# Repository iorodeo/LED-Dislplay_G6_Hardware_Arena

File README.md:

## LED-Display\_ G6\_Hardware\_Arena 

This repository is part of <https://reiserlab.github.io/Modular-LED-Display/>.
It contains the KiCad design and production files for the G6 arena hardware.

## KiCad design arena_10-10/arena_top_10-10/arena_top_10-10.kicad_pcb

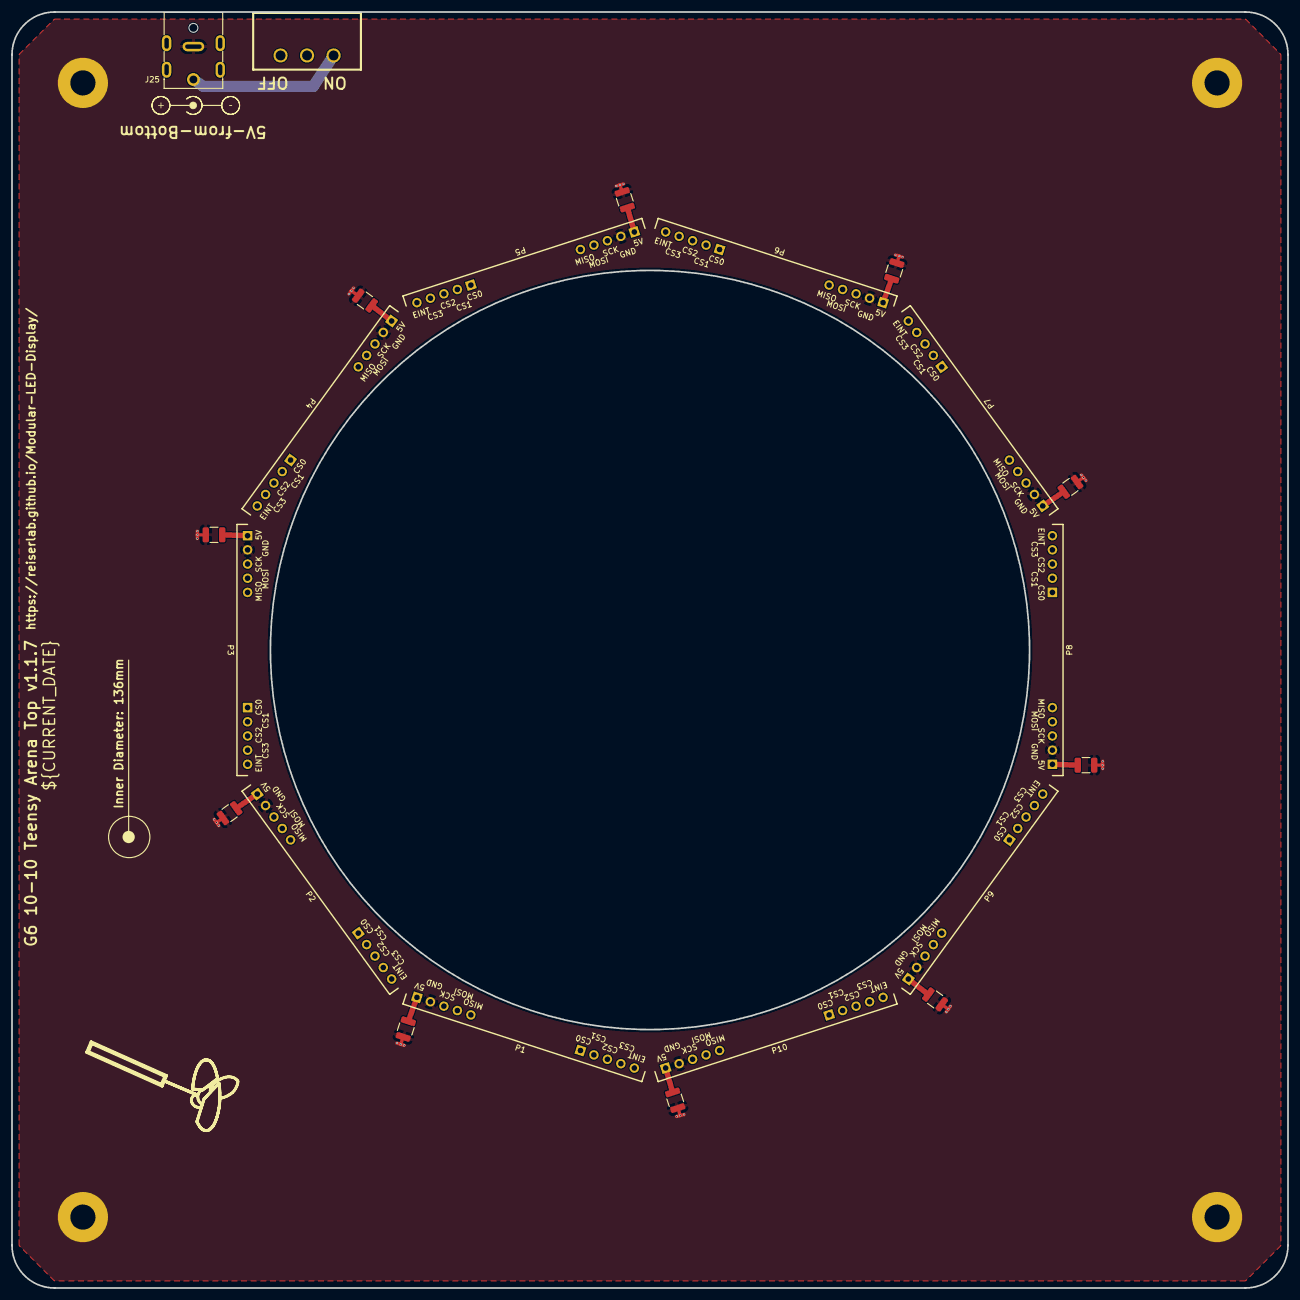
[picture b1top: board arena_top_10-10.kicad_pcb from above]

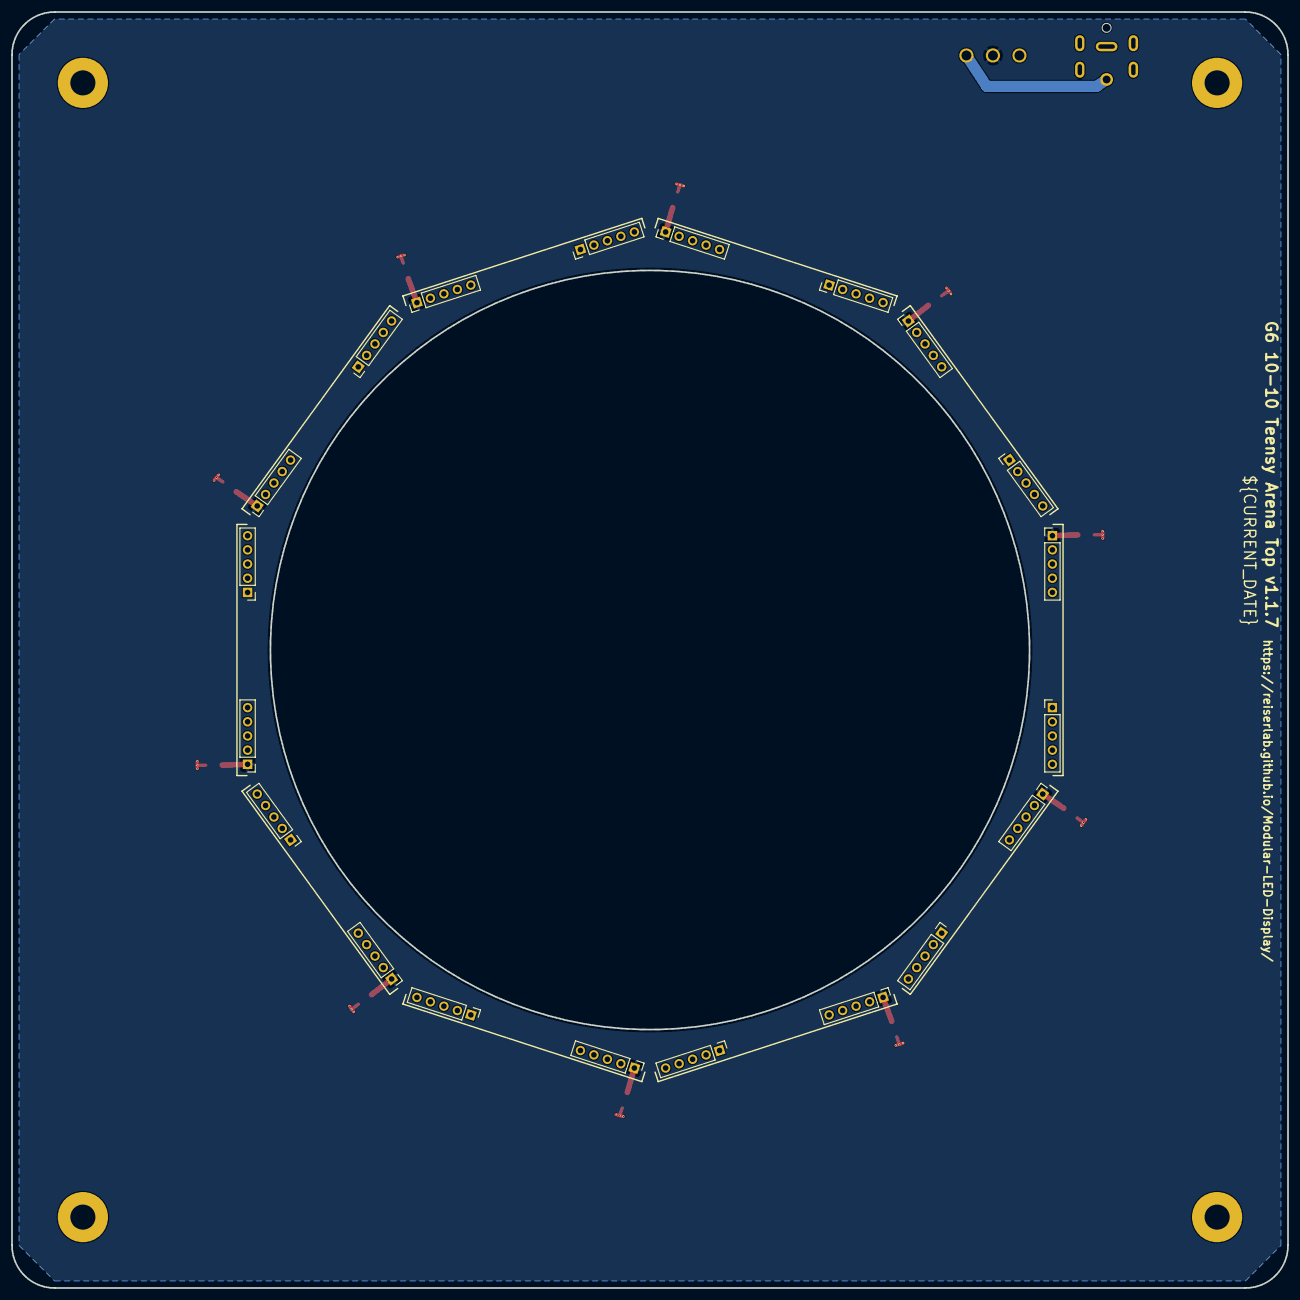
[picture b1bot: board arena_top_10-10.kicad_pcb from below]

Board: 2 copper layers, 228.6 x 228.6 mm, 46 parts (20 on the bottom side), 3 nets.

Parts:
C42, C47, C52, C57, C62, C67, C72, C77, C82, C87: 100uF; C_1210_3225Metric
H1, H2, H3, H4: MountingHole_Pad; MountingHole_4.5mm_Pad
J5, J6, J7, J8, J9, J10, J11, J12, J13, J14, J15, J16, J17, J18, J19, J20, J21, J22, J23, J24: Conn_01x05; PinHeader_1x05_P2.54mm_Vertical
J25: Barrel_Jack; DC-053D-20A
P1, P2, P3, P4, P5, P6, P7, P8, P9, P10: NA; Panel_Silk
SW1: SW_SPDT; slide_switch

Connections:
+5V: C42.2, C47.2, C52.2, C57.2, C62.2, C67.2, C72.2, C77.2, C82.2, C87.2, J5.1, J7.1, J9.1, J11.1, J13.1, J15.1, J17.1, J19.1, J21.1, J23.1, SW1.2 (B)
/Power/SW_5V: J25.1, SW1.1 (A)
GND: C42.1, C47.1, C52.1, C57.1, C62.1, C67.1, C72.1, C77.1, C82.1, C87.1, H1.1, H2.1, H3.1, H4.1, J5.2, J7.2, J9.2, J11.2, J13.2, J15.2, J17.2, J19.2, J21.2, J23.2, J25.2

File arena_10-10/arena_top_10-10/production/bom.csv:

Designator,Footprint,Quantity,Value,LCSC Part #
"C42, C47, C52, C57, C62, C67, C72, C77, C82, C87",1210,10,100uF,C7432790
"J10, J11, J12, J13, J14, J15, J16, J17, J18, J19, J20, J21, J22, J23, J24, J5, J6, J7, J8, J9",PinHeader_1x05_P2.54mm_Vertical,20,Conn_01x05,C492404
J25,DC-053D-20A,1,Barrel_Jack,C707274
SW1,slide_switch,1,SW_SPDT,C19189125

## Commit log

2026-02-26 Project creation.
2026-02-27 Re-worked MISO handling and analog input circuit.
    Modified so that MISO isolation circuits are in fan out section and
    are such that they will be placed close to the teensy. Modified the
    analog input circuit so that the teensy MCU analog inputs are used in
    conjuction with a level shifting circuit.
2026-06-05 Pushed latest minor changes.
    Checked lscs parts numbers. Added some images. remade production files.
